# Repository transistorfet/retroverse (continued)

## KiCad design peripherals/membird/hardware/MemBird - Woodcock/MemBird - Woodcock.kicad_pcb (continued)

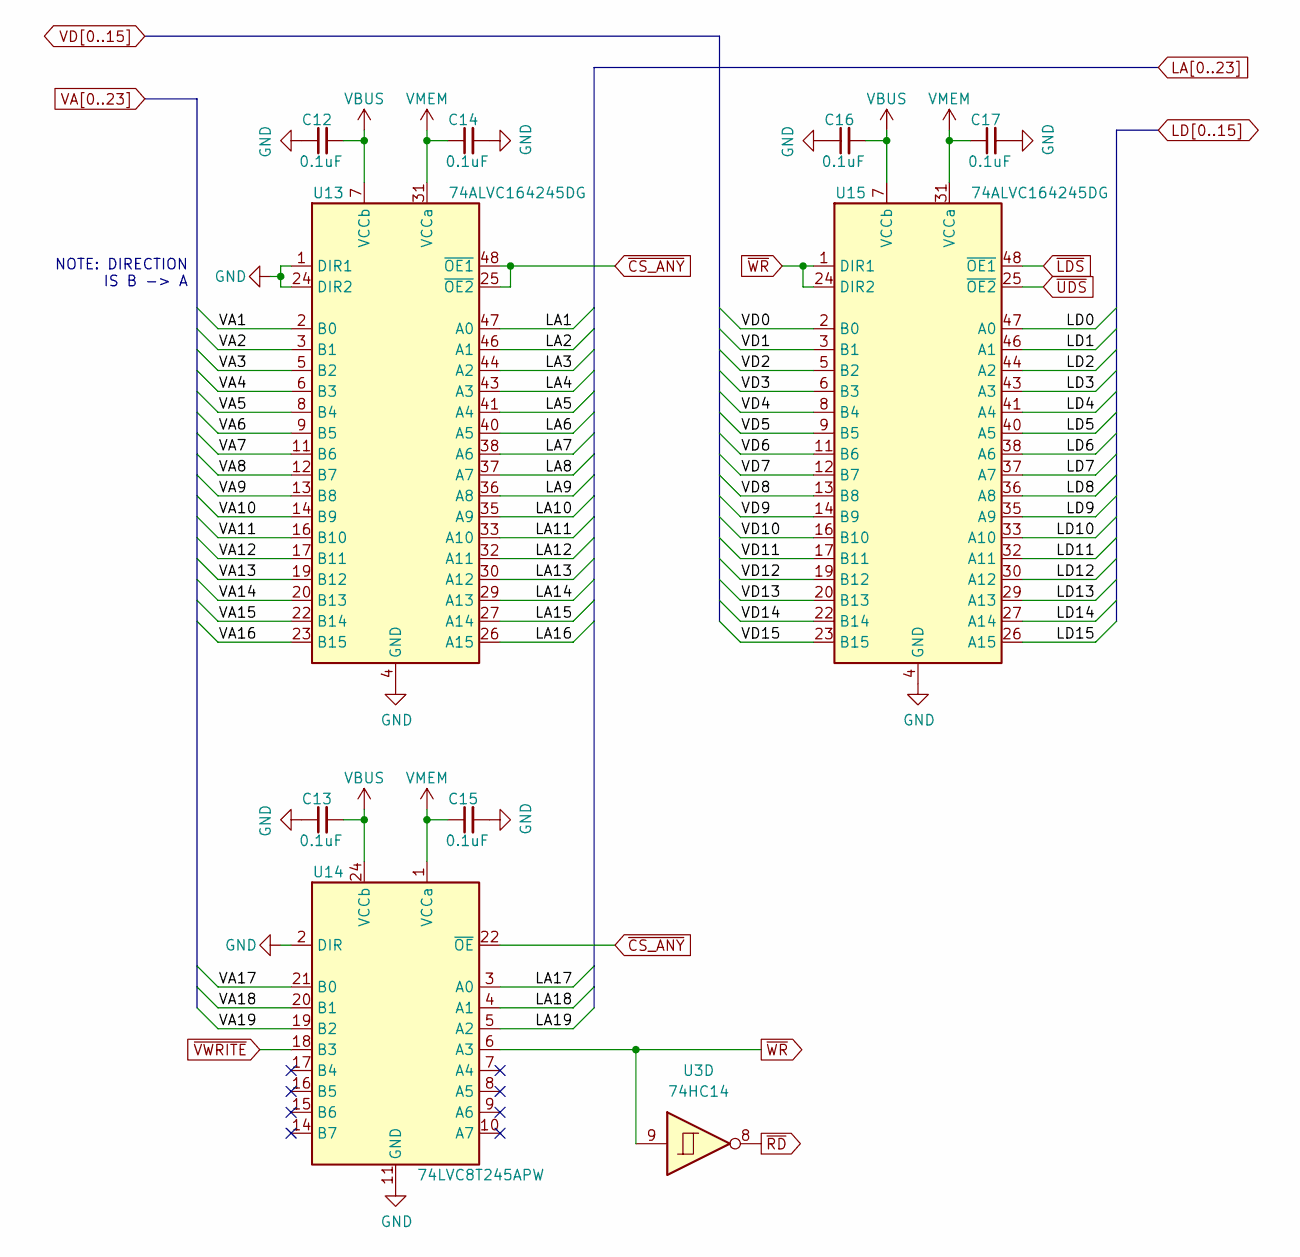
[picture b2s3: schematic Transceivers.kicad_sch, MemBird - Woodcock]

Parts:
C12, C13, C14, C15, C16, C17: 0.1uF; C_0805_2012Metric_Pad1.18x1.45mm_HandSolder
U3: 74HC14; TSSOP-14_4.4x5mm_P0.65mm
U13, U15: 74ALVC164245DG; TSSOP-48_6.1x12.5mm_P0.5mm
U14: 74LVC8T245APW; TSSOP-24_4.4x7.8mm_P0.65mm

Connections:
GND: C12.1, C13.1, C14.2, C15.2, C16.1, C17.2, U13.1 (DIR1), U13.4 (GND), U13.10 (GND), U13.15 (GND), U13.21 (GND), U13.24 (DIR2), U13.28 (GND), U13.34 (GND), U13.39 (GND), U13.45 (GND), U14.2 (DIR), U14.11 (GND), U14.12 (GND), U14.13 (GND), U15.4 (GND), U15.10 (GND), U15.15 (GND), U15.21 (GND), U15.28 (GND), U15.34 (GND), U15.39 (GND), U15.45 (GND); also elsewhere on the board
LA1: U13.47 (A0); also elsewhere on the board
LA2: U13.46 (A1); also elsewhere on the board
LA3: U13.44 (A2); also elsewhere on the board
LA4: U13.43 (A3); also elsewhere on the board
LA5: U13.41 (A4); also elsewhere on the board
LA6: U13.40 (A5); also elsewhere on the board
LA7: U13.38 (A6); also elsewhere on the board
LA8: U13.37 (A7); also elsewhere on the board
LA9: U13.36 (A8); also elsewhere on the board
LA10: U13.35 (A9); also elsewhere on the board
LA11: U13.33 (A10); also elsewhere on the board
LA12: U13.32 (A11); also elsewhere on the board
LA13: U13.30 (A12); also elsewhere on the board
LA14: U13.29 (A13); also elsewhere on the board
LA15: U13.27 (A14); also elsewhere on the board
LA16: U13.26 (A15); also elsewhere on the board
LA17: U14.3 (A0); also elsewhere on the board
LA18: U14.4 (A1); also elsewhere on the board
LA19: U14.5 (A2); also elsewhere on the board
LD0: U15.47 (A0); also elsewhere on the board
LD1: U15.46 (A1); also elsewhere on the board
LD2: U15.44 (A2); also elsewhere on the board
LD3: U15.43 (A3); also elsewhere on the board
LD4: U15.41 (A4); also elsewhere on the board
LD5: U15.40 (A5); also elsewhere on the board
LD6: U15.38 (A6); also elsewhere on the board
LD7: U15.37 (A7); also elsewhere on the board
LD8: U15.36 (A8); also elsewhere on the board
LD9: U15.35 (A9); also elsewhere on the board
LD10: U15.33 (A10); also elsewhere on the board
LD11: U15.32 (A11); also elsewhere on the board
LD12: U15.30 (A12); also elsewhere on the board
LD13: U15.29 (A13); also elsewhere on the board
LD14: U15.27 (A14); also elsewhere on the board
LD15: U15.26 (A15); also elsewhere on the board
VA1: U13.2 (B0); also elsewhere on the board
VA2: U13.3 (B1); also elsewhere on the board
VA3: U13.5 (B2); also elsewhere on the board
VA4: U13.6 (B3); also elsewhere on the board
VA5: U13.8 (B4); also elsewhere on the board
VA6: U13.9 (B5); also elsewhere on the board
VA7: U13.11 (B6); also elsewhere on the board
VA8: U13.12 (B7); also elsewhere on the board
VA9: U13.13 (B8); also elsewhere on the board
VA10: U13.14 (B9); also elsewhere on the board
VA11: U13.16 (B10); also elsewhere on the board
VA12: U13.17 (B11); also elsewhere on the board
VA13: U13.19 (B12); also elsewhere on the board
VA14: U13.20 (B13); also elsewhere on the board
VA15: U13.22 (B14); also elsewhere on the board
VA16: U13.23 (B15); also elsewhere on the board
VA17: U14.21 (B0); also elsewhere on the board
VA18: U14.20 (B1); also elsewhere on the board
VA19: U14.19 (B2); also elsewhere on the board
VBUS: C12.2, C13.2, C16.2, U13.7 (VCCb), U13.18 (VCCb), U14.23 (VCCb), U14.24 (VCCb), U15.7 (VCCb), U15.18 (VCCb); also elsewhere on the board
VD0: U15.2 (B0); also elsewhere on the board
VD1: U15.3 (B1); also elsewhere on the board
VD2: U15.5 (B2); also elsewhere on the board
VD3: U15.6 (B3); also elsewhere on the board
VD4: U15.8 (B4); also elsewhere on the board
VD5: U15.9 (B5); also elsewhere on the board
VD6: U15.11 (B6); also elsewhere on the board
VD7: U15.12 (B7); also elsewhere on the board
VD8: U15.13 (B8); also elsewhere on the board
VD9: U15.14 (B9); also elsewhere on the board
VD10: U15.16 (B10); also elsewhere on the board
VD11: U15.17 (B11); also elsewhere on the board
VD12: U15.19 (B12); also elsewhere on the board
VD13: U15.20 (B13); also elsewhere on the board
VD14: U15.22 (B14); also elsewhere on the board
VD15: U15.23 (B15); also elsewhere on the board
VMEM: C14.1, C15.1, C17.1, U13.31 (VCCa), U13.42 (VCCa), U14.1 (VCCa), U15.31 (VCCa), U15.42 (VCCa); also elsewhere on the board
~CS_ANY: U13.25 (~OE2), U13.48 (~OE1), U14.22 (~OE); also elsewhere on the board
~LDS: U15.48 (~OE1); also elsewhere on the board
~RD: U3.8; also elsewhere on the board
~UDS: U15.25 (~OE2); also elsewhere on the board
~VWRITE: U14.18 (B3); also elsewhere on the board
~WR: U3.9, U14.6 (A3), U15.1 (DIR1), U15.24 (DIR2); also elsewhere on the board

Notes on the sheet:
NOTE: DIRECTION IS B -> A

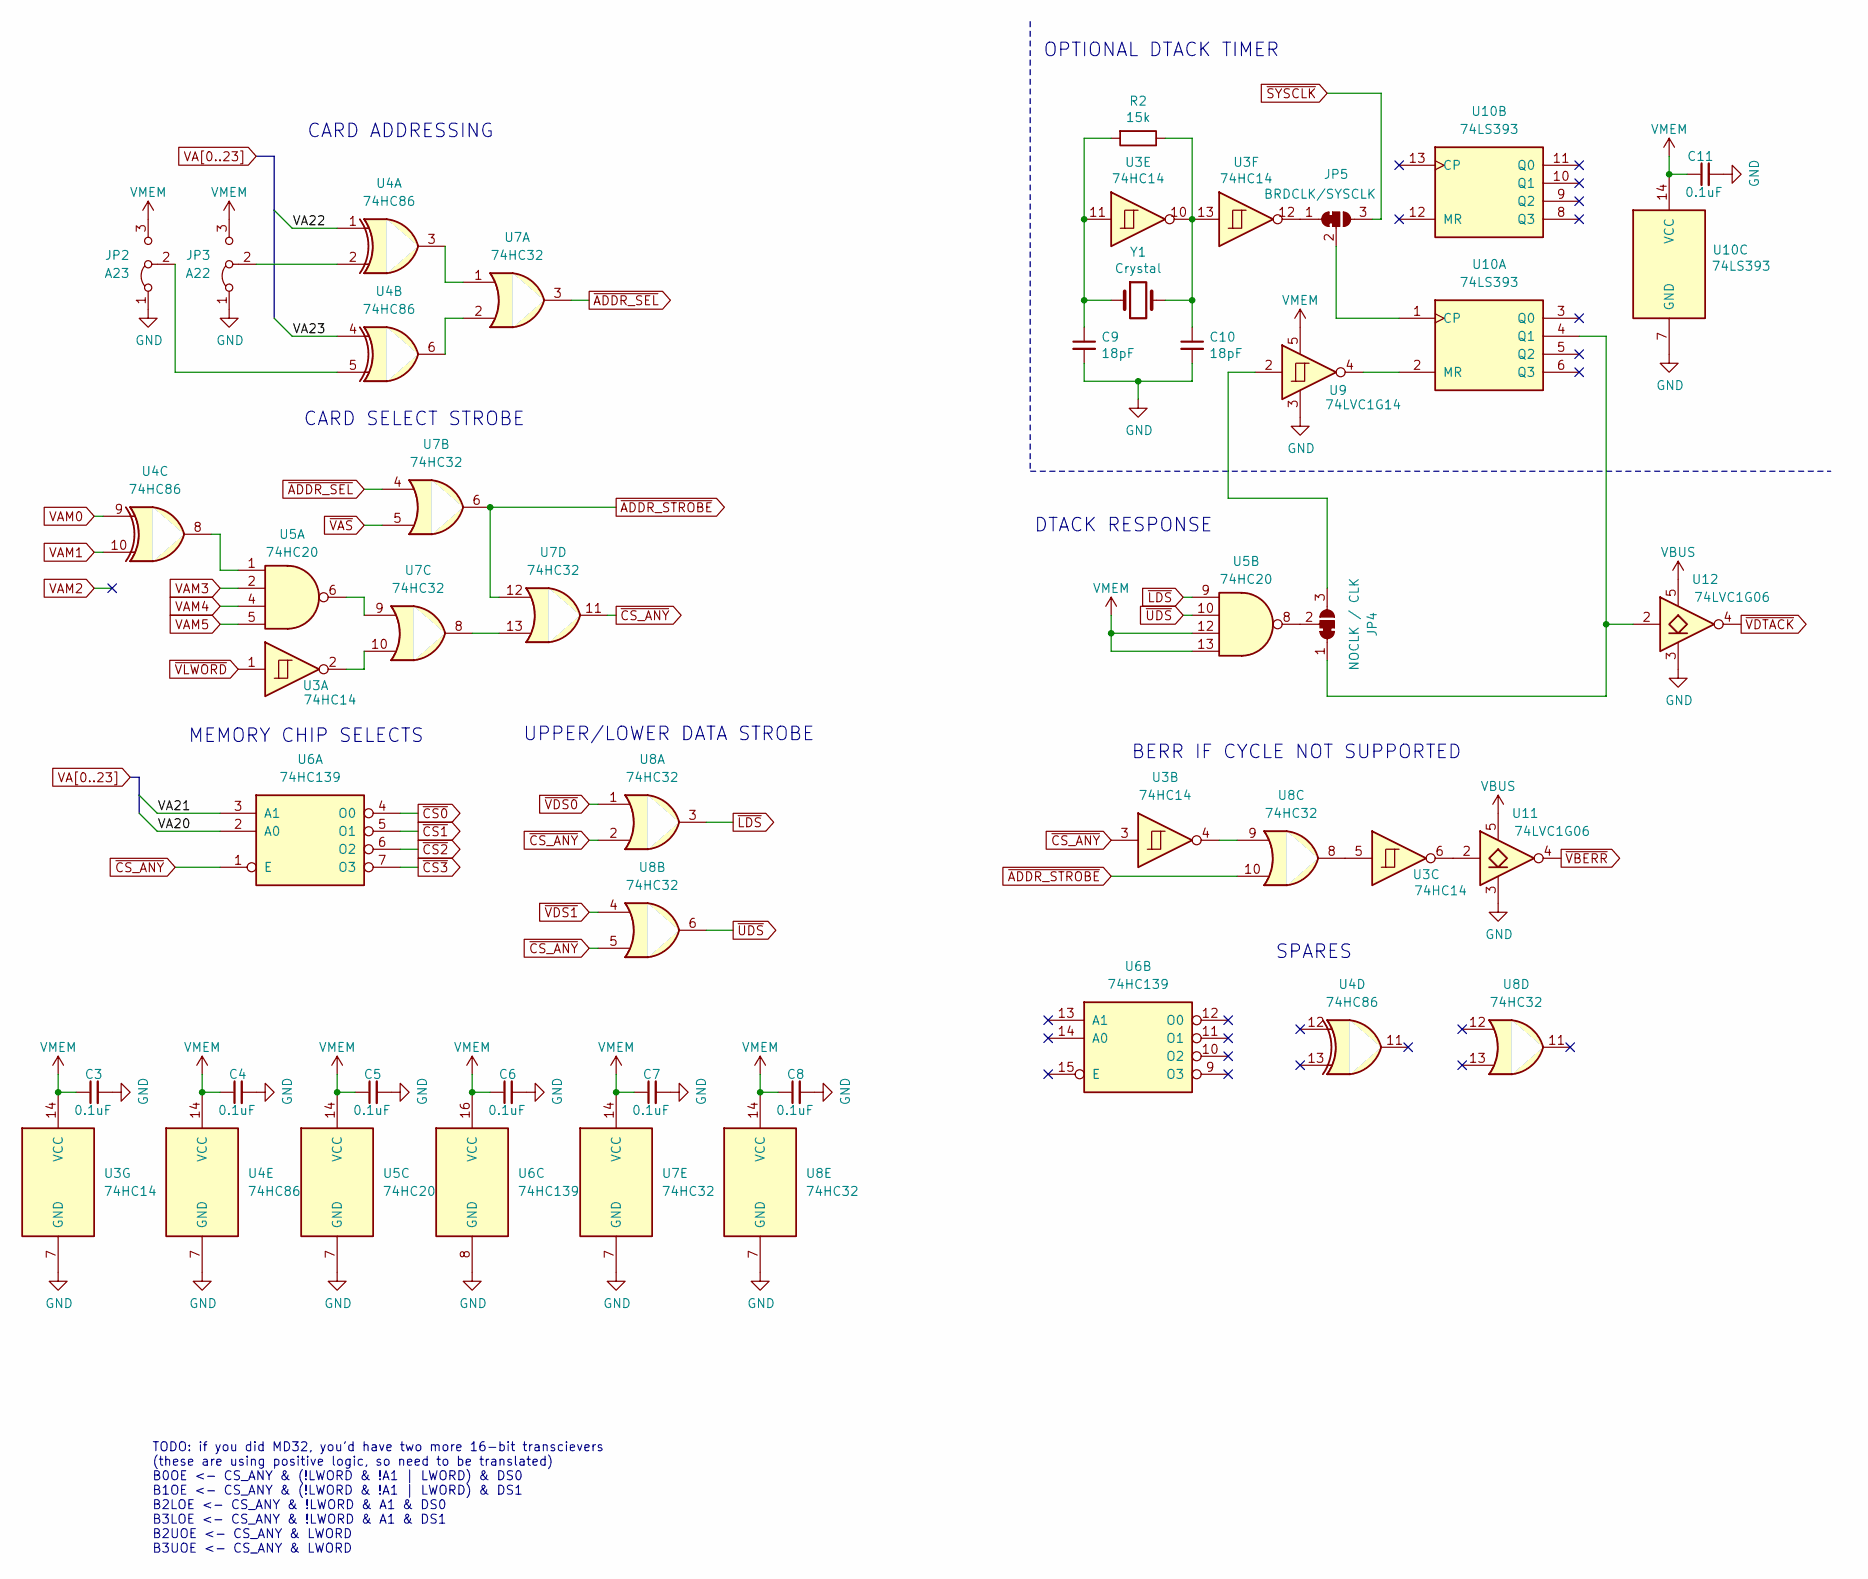
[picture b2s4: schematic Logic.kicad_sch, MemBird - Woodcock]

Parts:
C3, C4, C5, C6, C7, C8, C11: 0.1uF; C_0805_2012Metric_Pad1.18x1.45mm_HandSolder
C9, C10: 18pF; C_Disc_D3.0mm_W2.0mm_P2.50mm
JP2: A23; PinHeader_1x03_P2.54mm_Vertical
JP3: A22; PinHeader_1x03_P2.54mm_Vertical
JP4: NOCLK / CLK; SolderJumper-3_P1.3mm_Bridged12_RoundedPad1.0x1.5mm_NumberL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
JP5: BRDCLK/SYSCLK; SolderJumper-3_P1.3mm_Bridged12_RoundedPad1.0x1.5mm_NumberL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
R2: 15k; R_0805_2012Metric_Pad1.20x1.40mm_HandSolder
U3: 74HC14; TSSOP-14_4.4x5mm_P0.65mm
U4: 74HC86; TSSOP-14_4.4x5mm_P0.65mm
U5: 74HC20; TSSOP-14_4.4x5mm_P0.65mm
U6: 74HC139; TSSOP-16_4.4x5mm_P0.65mm
U7, U8: 74HC32; TSSOP-14_4.4x5mm_P0.65mm
U9: 74LVC1G14; SOT-353_SC-70-5_Handsoldering
U10: 74LS393; TSSOP-14_4.4x5mm_P0.65mm
U11, U12: 74LVC1G06; SOT-353_SC-70-5_Handsoldering
Y1: Crystal; Crystal_HC49-4H_Vertical

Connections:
GND: C3.2, C4.2, C5.2, C6.2, C7.2, C8.2, C9.2, C10.2, C11.2, JP2.1 (A), JP3.1 (A), U3.7 (GND), U4.7 (GND), U5.7 (GND), U6.8 (GND), U7.7 (GND), U8.7 (GND), U9.3, U10.7 (GND), U11.3, U12.3; also elsewhere on the board
unnamed: C9.1, R2.2, U3.11, Y1.1
unnamed: C10.1, R2.1, U3.10, U3.13, Y1.2
unnamed: JP2.2 (C), U4.5
unnamed: JP3.2 (C), U4.2
unnamed: JP4.1 (A), U10.4 (Q1), U12.2
unnamed: JP4.3 (B), U9.2
unnamed: JP4.2 (C), U5.8
unnamed: JP5.1 (A), U3.12
unnamed: JP5.2 (C), U10.1 (CP)
unnamed: U3.2, U7.10
unnamed: U3.4, U8.9
unnamed: U3.5, U8.8
unnamed: U4.3, U7.1
unnamed: U4.6, U7.2
unnamed: U4.8, U5.1
unnamed: U5.6, U7.9
unnamed: U7.8, U7.13
unnamed: U9.4, U10.2 (MR)
unnamed: U3.6, U11.2
VA20: U6.2 (A0); also elsewhere on the board
VA21: U6.3 (A1); also elsewhere on the board
VA22: U4.1; also elsewhere on the board
VA23: U4.4; also elsewhere on the board
VAM0: U4.9; also elsewhere on the board
VAM1: U4.10; also elsewhere on the board
VAM3: U5.2; also elsewhere on the board
VAM4: U5.4; also elsewhere on the board
VAM5: U5.5; also elsewhere on the board
VBUS: U11.5, U12.5; also elsewhere on the board
VMEM: C3.1, C4.1, C5.1, C6.1, C7.1, C8.1, C11.1, JP2.3 (B), JP3.3 (B), U3.14 (VCC), U4.14 (VCC), U5.12, U5.13, U5.14 (VCC), U6.16 (VCC), U7.14 (VCC), U8.14 (VCC), U9.5, U10.14 (VCC); also elsewhere on the board
~ADDR_SEL: U7.3, U7.4
~ADDR_STROBE: U7.6, U7.12, U8.10
~CS0: U6.4 (O0); also elsewhere on the board
~CS1: U6.5 (O1); also elsewhere on the board
~CS2: U6.6 (O2); also elsewhere on the board
~CS3: U6.7 (O3); also elsewhere on the board
~CS_ANY: U3.3, U6.1 (E), U7.11, U8.2, U8.5; also elsewhere on the board
~LDS: U5.9, U8.3; also elsewhere on the board
~SYSCLK: JP5.3 (B); also elsewhere on the board
~UDS: U5.10, U8.6; also elsewhere on the board
~VAS: U7.5; also elsewhere on the board
~VBERR: U11.4; also elsewhere on the board
~VDS0: U8.1; also elsewhere on the board
~VDS1: U8.4; also elsewhere on the board
~VDTACK: U12.4; also elsewhere on the board
~VLWORD: U3.1; also elsewhere on the board

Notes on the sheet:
TODO: if you did MD32, you'd have two more 16-bit transcievers (these are using positive logic, so need to be translated) B0OE <- CS_ANY & (!LWORD & !A1 | LWORD) & DS0 B1OE <- CS_ANY & (!LWORD & !A1 | LWORD) & DS1 B2LOE <- CS_ANY & !LWORD & A1 & DS0 B3LOE <- CS_ANY & !LWORD & A1 & DS1 B2UOE <- CS_A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
MEMORY CHIP SELECTS
BERR IF CYCLE NOT SUPPORTED
SPARES
DTACK RESPONSE
OPTIONAL DTACK TIMER
CARD ADDRESSING
CARD SELECT STROBE
UPPER/LOWER DATA STROBE

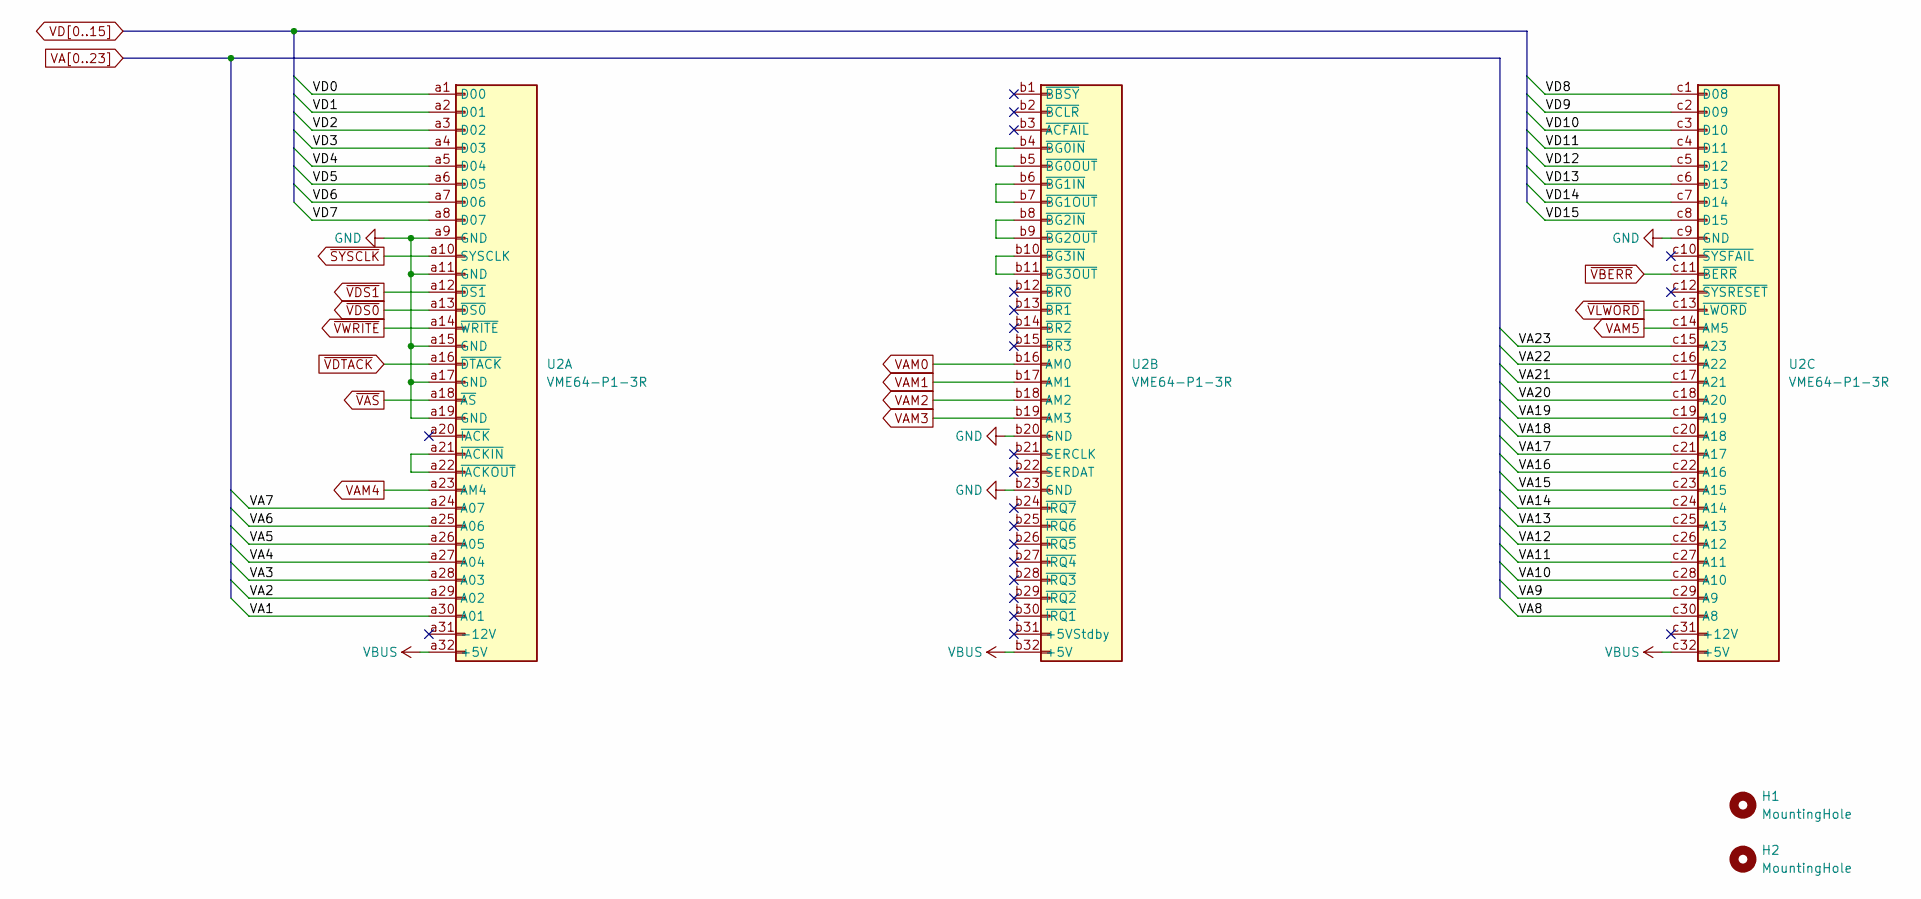
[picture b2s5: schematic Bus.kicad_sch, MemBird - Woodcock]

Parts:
H1, H2: MountingHole; MountingHole_2.7mm_M2.5_DIN965
U2: VME64-P1-3R; DIN41612_C_3x32_Male_Horizontal_THT

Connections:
GND: U2.a9 (GND), U2.a11 (GND), U2.a15 (GND), U2.a17 (GND), U2.a19 (GND), U2.b20 (GND), U2.b23 (GND), U2.c9 (GND); also elsewhere on the board
unnamed: U2.a21 (~IACKIN), U2.a22 (~IACKOUT)
unnamed: U2.b4 (~BG0IN), U2.b5 (~BG0OUT)
unnamed: U2.b6 (~BG1IN), U2.b7 (~BG1OUT)
unnamed: U2.b8 (~BG2IN), U2.b9 (~BG2OUT)
unnamed: U2.b10 (~BG3IN), U2.b11 (~BG3OUT)
VA1: U2.a30 (A01); also elsewhere on the board
VA2: U2.a29 (A02); also elsewhere on the board
VA3: U2.a28 (A03); also elsewhere on the board
VA4: U2.a27 (A04); also elsewhere on the board
VA5: U2.a26 (A05); also elsewhere on the board
VA6: U2.a25 (A06); also elsewhere on the board
VA7: U2.a24 (A07); also elsewhere on the board
VA8: U2.c30 (A8); also elsewhere on the board
VA9: U2.c29 (A9); also elsewhere on the board
VA10: U2.c28 (A10); also elsewhere on the board
VA11: U2.c27 (A11); also elsewhere on the board
VA12: U2.c26 (A12); also elsewhere on the board
VA13: U2.c25 (A13); also elsewhere on the board
VA14: U2.c24 (A14); also elsewhere on the board
VA15: U2.c23 (A15); also elsewhere on the board
VA16: U2.c22 (A16); also elsewhere on the board
VA17: U2.c21 (A17); also elsewhere on the board
VA18: U2.c20 (A18); also elsewhere on the board
VA19: U2.c19 (A19); also elsewhere on the board
VA20: U2.c18 (A20); also elsewhere on the board
VA21: U2.c17 (A21); also elsewhere on the board
VA22: U2.c16 (A22); also elsewhere on the board
VA23: U2.c15 (A23); also elsewhere on the board
VAM0: U2.b16 (AM0); also elsewhere on the board
VAM1: U2.b17 (AM1); also elsewhere on the board
VAM2: U2.b18 (AM2)
VAM3: U2.b19 (AM3); also elsewhere on the board
VAM4: U2.a23 (AM4); also elsewhere on the board
VAM5: U2.c14 (AM5); also elsewhere on the board
VBUS: U2.a32 (+5V), U2.b32 (+5V), U2.c32 (+5V); also elsewhere on the board
VD0: U2.a1 (D00); also elsewhere on the board
VD1: U2.a2 (D01); also elsewhere on the board
VD2: U2.a3 (D02); also elsewhere on the board
VD3: U2.a4 (D03); also elsewhere on the board
VD4: U2.a5 (D04); also elsewhere on the board
VD5: U2.a6 (D05); also elsewhere on the board
VD6: U2.a7 (D06); also elsewhere on the board
VD7: U2.a8 (D07); also elsewhere on the board
VD8: U2.c1 (D08); also elsewhere on the board
VD9: U2.c2 (D09); also elsewhere on the board
VD10: U2.c3 (D10); also elsewhere on the board
VD11: U2.c4 (D11); also elsewhere on the board
VD12: U2.c5 (D12); also elsewhere on the board
VD13: U2.c6 (D13); also elsewhere on the board
VD14: U2.c7 (D14); also elsewhere on the board
VD15: U2.c8 (D15); also elsewhere on the board
~SYSCLK: U2.a10 (SYSCLK); also elsewhere on the board
~VAS: U2.a18 (~AS); also elsewhere on the board
~VBERR: U2.c11 (~BERR); also elsewhere on the board
~VDS0: U2.a13 (~DS0); also elsewhere on the board
~VDS1: U2.a12 (~DS1); also elsewhere on the board
~VDTACK: U2.a16 (~DTACK); also elsewhere on the board
~VLWORD: U2.c13 (~LWORD); also elsewhere on the board
~VWRITE: U2.a14 (~WRITE); also elsewhere on the board

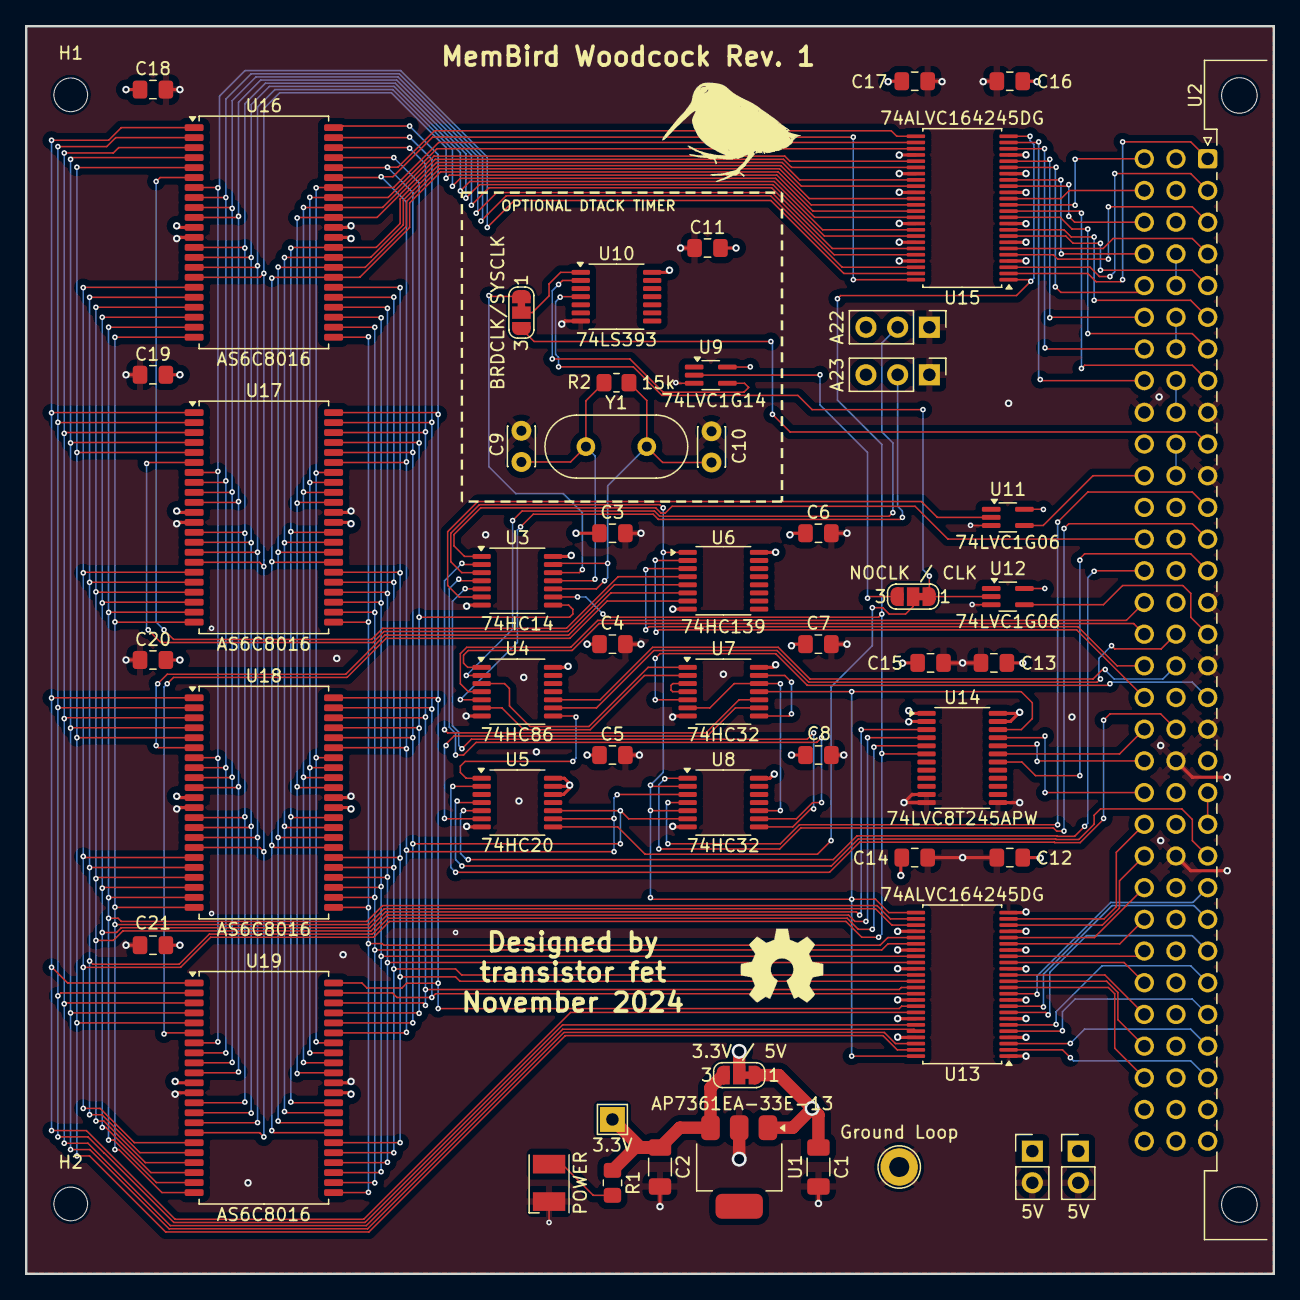
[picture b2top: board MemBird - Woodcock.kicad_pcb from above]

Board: 4 copper layers, 100.0 x 100.0 mm, 56 parts (0 on the bottom side), 127 nets.
